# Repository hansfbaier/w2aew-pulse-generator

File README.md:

# w2aew-pulse-generator
Realization of a fast rise-time pulse generator design by W2AEW

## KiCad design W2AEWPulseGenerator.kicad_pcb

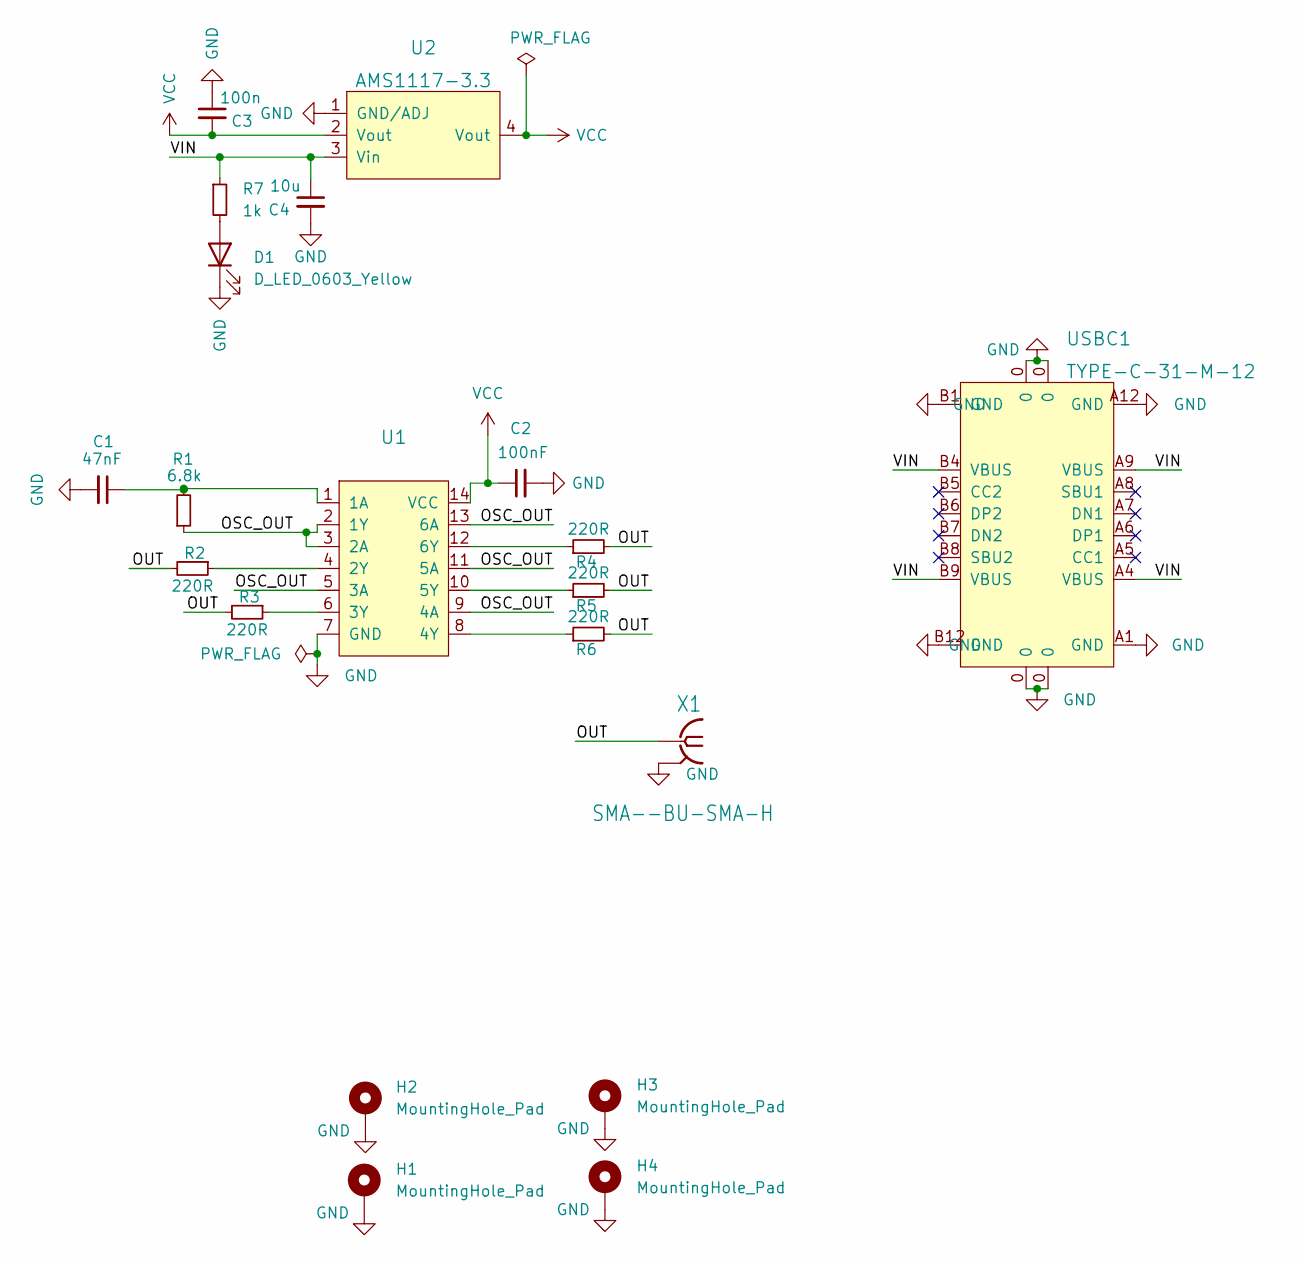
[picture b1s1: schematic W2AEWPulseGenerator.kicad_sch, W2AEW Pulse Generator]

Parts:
C1: 47nF; C_0603_1608Metric; LCSC C1622
C2: 100nF; C_0402_1005Metric; LCSC C1525
C3: 100n; C_0805_2012Metric; LCSC C49678
C4: 10u; C_0805_2012Metric; LCSC C15850
D1: D_LED_0603_Yellow; LED_0603_1608Metric; LCSC C72038
H1, H2, H3, H4: MountingHole_Pad; MountingHole_2.2mm_M2_Pad_Via
R1: 6.8k; R_0402_1005Metric; LCSC C25917
R2, R3, R4, R5, R6: 220R; R_0402_1005Metric; LCSC C25091
R7: 1k; R_0402_1005Metric; LCSC C11702
U1: LCSC Part C7619
U2: AMS1117-3.3; SOT-223-3_L6.5-W3.4-P2.30-LS7.0-BR; LCSC Part C6186
USBC1: TYPE-C-31-M-12; USB-C_SMD-TYPE-C-31-M-12; LCSC Part C165948
X1: SMA--BU-SMA-H; SMA-TH_HJ-SMA014; LCSC C1509230

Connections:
/OSC_OUT: R1.1, U1.2 (1Y), U1.3 (2A), U1.5 (3A), U1.9 (4A), U1.11 (5A), U1.13 (6A)
/OUT: R2.2, R3.2, R4.2, R5.2, R6.2, X1.1
/VIN: C4.1, R7.1, U2.3 (Vin), USBC1.A4 (VBUS), USBC1.A9 (VBUS), USBC1.B4 (VBUS), USBC1.B9 (VBUS)
GND: C1.2, C2.2, C3.1, C4.2, D1.1 (K), H1.1, H2.1, H3.1, H4.1, U1.7 (GND), U2.1 (GND/ADJ), USBC1.0, USBC1.A1 (GND), USBC1.A12 (GND), USBC1.B1 (GND), USBC1.B12 (GND), X1.2, X1.3 (2), X1.4 (2), X1.5 (2)
unnamed: C1.1, R1.2, U1.1 (1A)
unnamed: D1.2 (A), R7.2
unnamed: R2.1, U1.4 (2Y)
unnamed: R3.1, U1.6 (3Y)
unnamed: R4.1, U1.12 (6Y)
unnamed: R5.1, U1.10 (5Y)
unnamed: R6.1, U1.8 (4Y)
VCC: C2.1, C3.2, U1.14 (VCC), U2.2 (Vout), U2.4 (Vout)

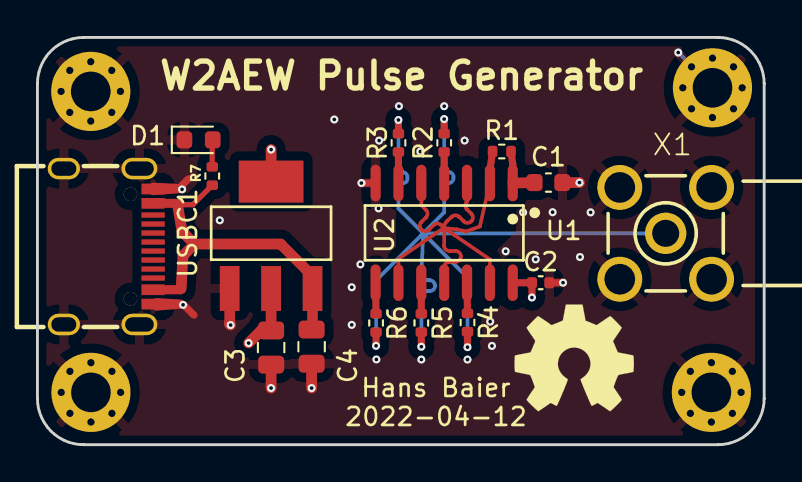
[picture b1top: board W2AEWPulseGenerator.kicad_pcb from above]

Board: 4 copper layers, 40.4 x 22.6 mm, 21 parts (0 on the bottom side), 12 nets.

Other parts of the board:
N1: OHWLOGO; OSHW-Symbol_6.7x6mm_SilkScreen

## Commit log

2022-04-28 add LICENSE
2022-04-28 fix DRC track spacing
